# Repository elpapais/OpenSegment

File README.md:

OpenSegment Serial Display
==========================

[  
*OpenSegment Serial Display (Yellow) (COM-11645)*](https://www.sparkfun.com/products/11645)

OpenSegment is a ATmega328 based backpack for larger 7-segment displays. The ATmega receives data over digital interfaces (such as TWI, UART, SPI and buttons) and does all the PWM and upkeep of the display. 

Larger 7-segment displays pull more power than a microcontroller is able to drive directly. OpenSegment has 8 PNP and 4 NPN transistors in order to drive the segments at their maximum brightness.

**Features:**
* Standard FTDI connection
* Arduino Pro Mini @ 8MHz bootloader
* 5V functionality

This part was created in Eagle 6.3

Repository Contents
-------------------
* **/Hardware** - All Eagle design files and 3D files(.brd, .sch,)
* **/Production** - Test bed files and production panel files
* **Note:** Firmware is not included in this repo. Please see the [Serial7SegmentDisplay repo](https://github.com/sparkfun/Serial7SegmentDisplay) for the firmware. 

Product Versions
----------------
* [COM-11644](https://www.sparkfun.com/products/11644)- Red display
* [COM-11645](https://www.sparkfun.com/products/11645) - Yellow display
* [COM-11646](https://www.sparkfun.com/products/11646) - Green display
* [COM-11647](https://www.sparkfun.com/products/11647) - Blue display
* [COM-11648](https://www.sparkfun.com/products/11648) - White display

License Information
-------------------
The hardware is released under [Creative Commons Share-alike 3.0](http://creativecommons.org/licenses/by-sa/3.0/).

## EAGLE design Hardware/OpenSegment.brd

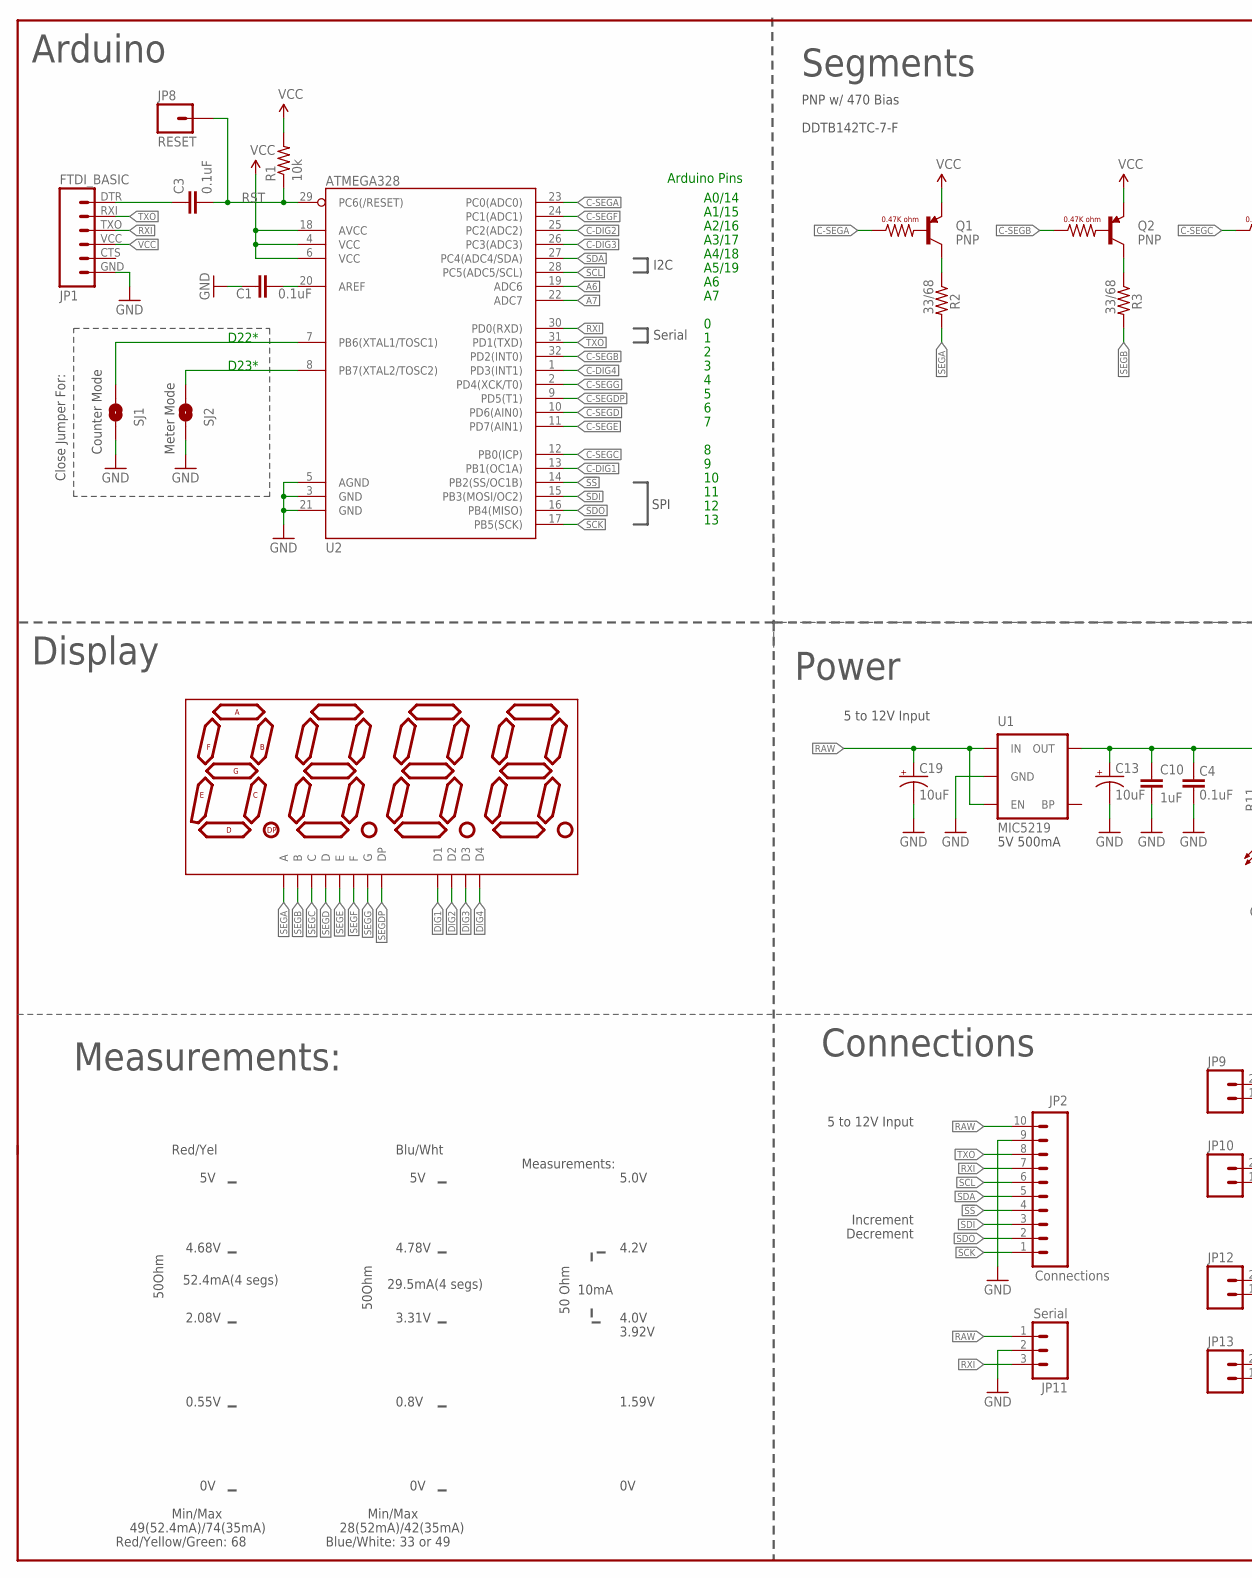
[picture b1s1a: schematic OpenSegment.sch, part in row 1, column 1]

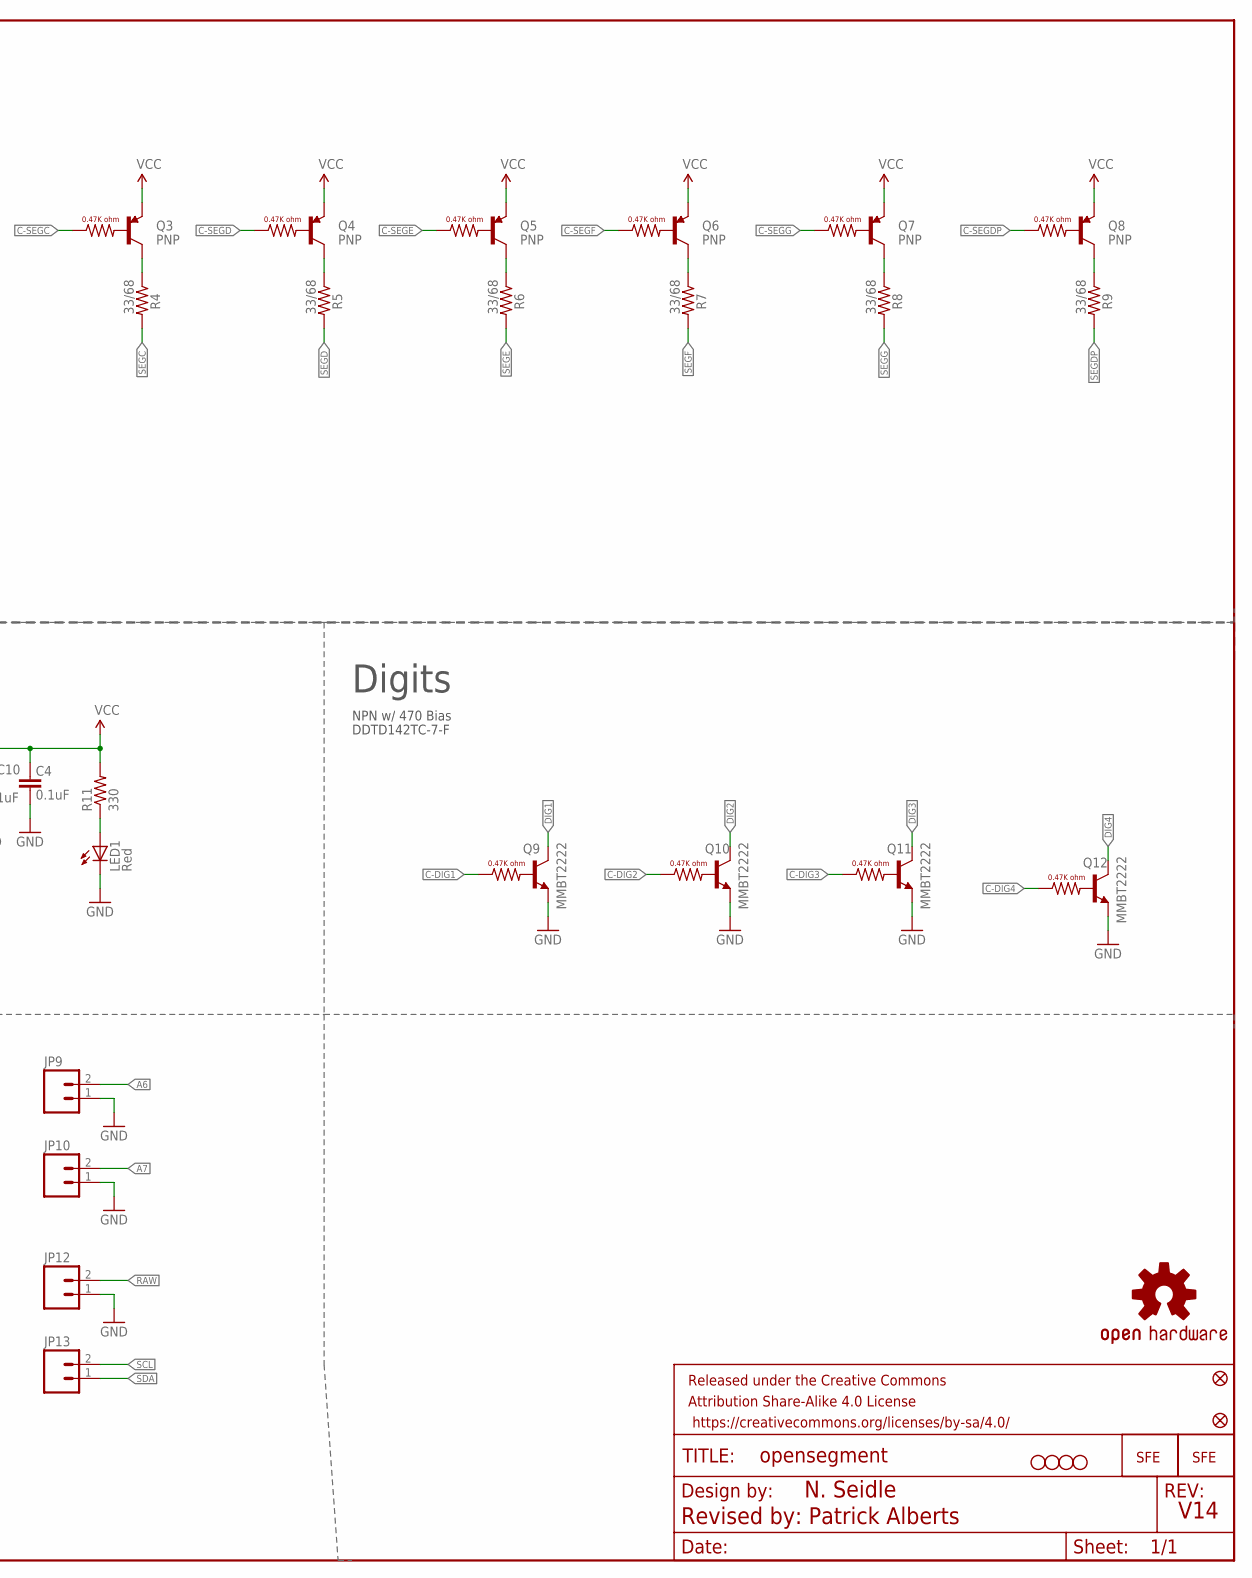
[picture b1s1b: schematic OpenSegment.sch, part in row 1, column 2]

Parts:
C1, C3, C4: 0.1uF; 0603-CAP
C10: 1uF; 0603-CAP
C13, C19: 10uF; EIA3216
FID1, FID2: FIDUCIAL1X2; FIDUCIAL-1X2
FRAME1: FRAME-LEDGER; CREATIVE_COMMONS
JP1: FTDI_BASIC
JP2: Connections; 1X10
JP3, JP4, JP5, JP6: STAND-OFF
JP8: RESET; 1X01
JP9, JP10, JP12, JP13: M02PTH; 1X02
JP11: Serial; JST-3-PTH
LED1: Red; LED-0603
Q1, Q2, Q3, Q4, Q5, Q6, Q7, Q8: PNP; SOT23-3
Q9, Q10, Q11, Q12: MMBT2222; SOT23-3
R1: 10k; 0603-RES
R2, R3, R4, R5, R6, R7, R8, R9: 33/68; 0603
R11: 330; 0603-RES
SJ1, SJ2: Counter Ctl; SJ_2S-NO
U1: MIC5219; SOT23-5
U2: ATMEGA328; TQFP32-08
U3: 7-SEGMENT-4DIGIT-COUNTERPTH; 7-SEGMENT-4DIGIT-COUNTER
U$2: LOGO-SFESK; SFE-LOGO-FLAME
U$4: OSHW-LOGOS; OSHW-LOGO-S
U$7: LOGO-SFENW2; SFE-NEW-WEB

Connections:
!SS: JP2.4, U2.14 (PB2(SS/OC1B))
A6: JP9.2, U2.19 (ADC6)
A7: JP10.2, U2.22 (ADC7)
ANALOG: SJ2.1, U2.8 (PB7(XTAL2/TOSC2))
C-DIG1: Q9.1 (B), U2.13 (PB1(OC1A))
C-DIG2: Q10.1 (B), U2.25 (PC2(ADC2))
C-DIG3: Q11.1 (B), U2.26 (PC3(ADC3))
C-DIG4: Q12.1 (B), U2.1 (PD3(INT1))
C-SEGA: Q1.1 (B), U2.23 (PC0(ADC0))
C-SEGB: Q2.1 (B), U2.32 (PD2(INT0))
C-SEGC: Q3.1 (B), U2.12 (PB0(ICP))
C-SEGD: Q4.1 (B), U2.10 (PD6(AIN0))
C-SEGDP: Q8.1 (B), U2.9 (PD5(T1))
C-SEGE: Q5.1 (B), U2.11 (PD7(AIN1))
C-SEGF: Q6.1 (B), U2.24 (PC1(ADC1))
C-SEGG: Q7.1 (B), U2.2 (PD4(XCK/T0))
COUNTER: SJ1.1, U2.7 (PB6(XTAL1/TOSC1))
DIG1: Q9.3 (C), U3.12 (D1)
DIG2: Q10.3 (C), U3.9 (D2)
DIG3: Q11.3 (C), U3.8 (D3)
DIG4: Q12.3 (C), U3.6 (D4)
GND: C1.1, C4.1, C10.2, C13.C (-), C19.C (-), JP1.GND (6), JP2.9, JP9.1, JP10.1, JP11.2, JP12.1, LED1.C, Q9.2 (E), Q10.2 (E), Q11.2 (E), Q12.2 (E), SJ1.2, SJ2.2, U1.2 (GND), U2.3 (GND), U2.5 (AGND), U2.21 (GND)
unnamed: Q1.3 (C), R2.1
unnamed: C3.1, JP1.DTR (1)
unnamed: Q2.3 (C), R3.1
unnamed: Q3.3 (C), R4.1
unnamed: Q4.3 (C), R5.1
unnamed: Q5.3 (C), R6.1
unnamed: Q6.3 (C), R7.1
unnamed: Q7.3 (C), R8.1
unnamed: Q8.3 (C), R9.1
unnamed: C1.2, U2.20 (AREF)
unnamed: LED1.A, R11.1
RAW: C19.A (+), JP2.10, JP11.1, JP12.2, U1.1 (IN), U1.3 (EN)
RST: C3.2, JP8.1, R1.1, U2.29 (PC6(/RESET))
RXI: JP1.TXO (3), JP2.7, JP11.3, U2.30 (PD0(RXD))
SCK: JP2.1, U2.17 (PB5(SCK))
SCL: JP2.6, JP13.2, U2.28 (PC5(ADC5/SCL))
SDA: JP2.5, JP13.1, U2.27 (PC4(ADC4/SDA))
SDI: JP2.3, U2.15 (PB3(MOSI/OC2))
SDO: JP2.2, U2.16 (PB4(MISO))
SEGA: R2.2, U3.11 (A)
SEGB: R3.2, U3.7 (B)
SEGC: R4.2, U3.4 (C)
SEGD: R5.2, U3.2 (D)
SEGDP: R9.2, U3.3 (DP)
SEGE: R6.2, U3.1 (E)
SEGF: R7.2, U3.10 (F)
SEGG: R8.2, U3.5 (G)
TXO: JP1.RXI (2), JP2.8, U2.31 (PD1(TXD))
VCC: C4.2, C10.1, C13.A (+), JP1.VCC (4), Q1.2 (E), Q2.2 (E), Q3.2 (E), Q4.2 (E), Q5.2 (E), Q6.2 (E), Q7.2 (E), Q8.2 (E), R1.2, R11.2, U1.5 (OUT), U2.4 (VCC), U2.6 (VCC), U2.18 (AVCC)

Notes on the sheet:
A0/14
A1/15
A2/16
A3/17
A4/18
A5/19
Arduino Pins
5V 500mA
SPI
Serial
I2C
Counter Mode
Arduino
Display
Segments
Digits
Connections
Power
D22*
D23*
4.2V
5.0V
4.0V
1.59V
3.92V
Measurements:
10mA
5 to 12V Input
Close Jumper For:
Meter Mode
Increment
Decrement
50 Ohm
4.78V
3.31V
0.8V
Blu/Wht
Red/Yel
4.68V
2.08V

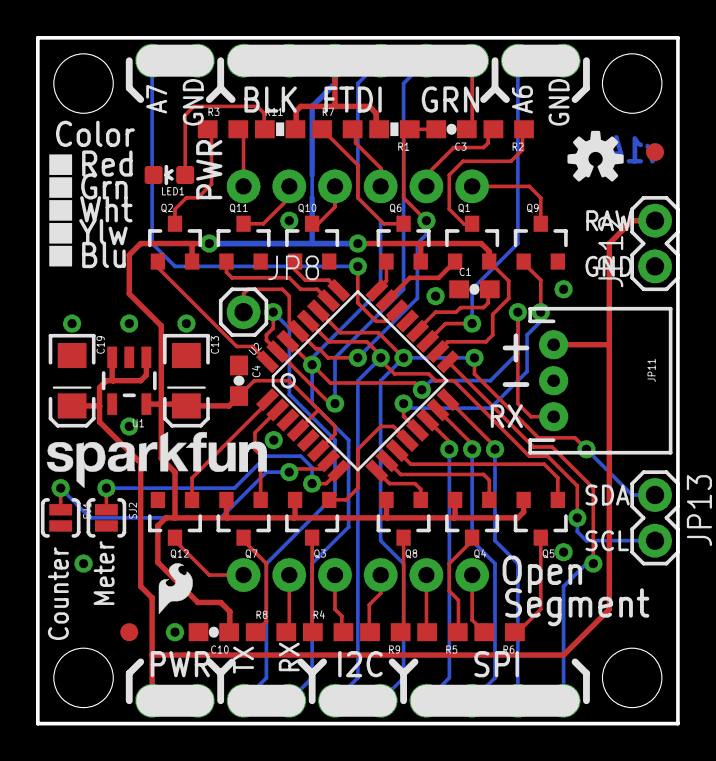
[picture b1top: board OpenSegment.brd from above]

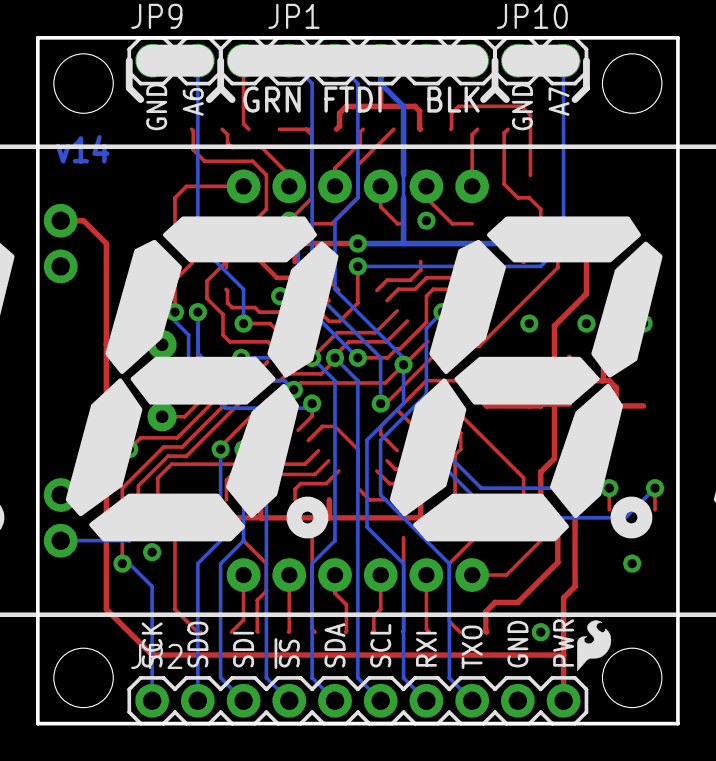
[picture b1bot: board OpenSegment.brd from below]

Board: 2 copper layers, 35.6 x 38.1 mm, 53 parts (6 on the bottom side), 51 nets.

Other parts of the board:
U$1: LOGO-SFESK; SFE-LOGO-FLAME

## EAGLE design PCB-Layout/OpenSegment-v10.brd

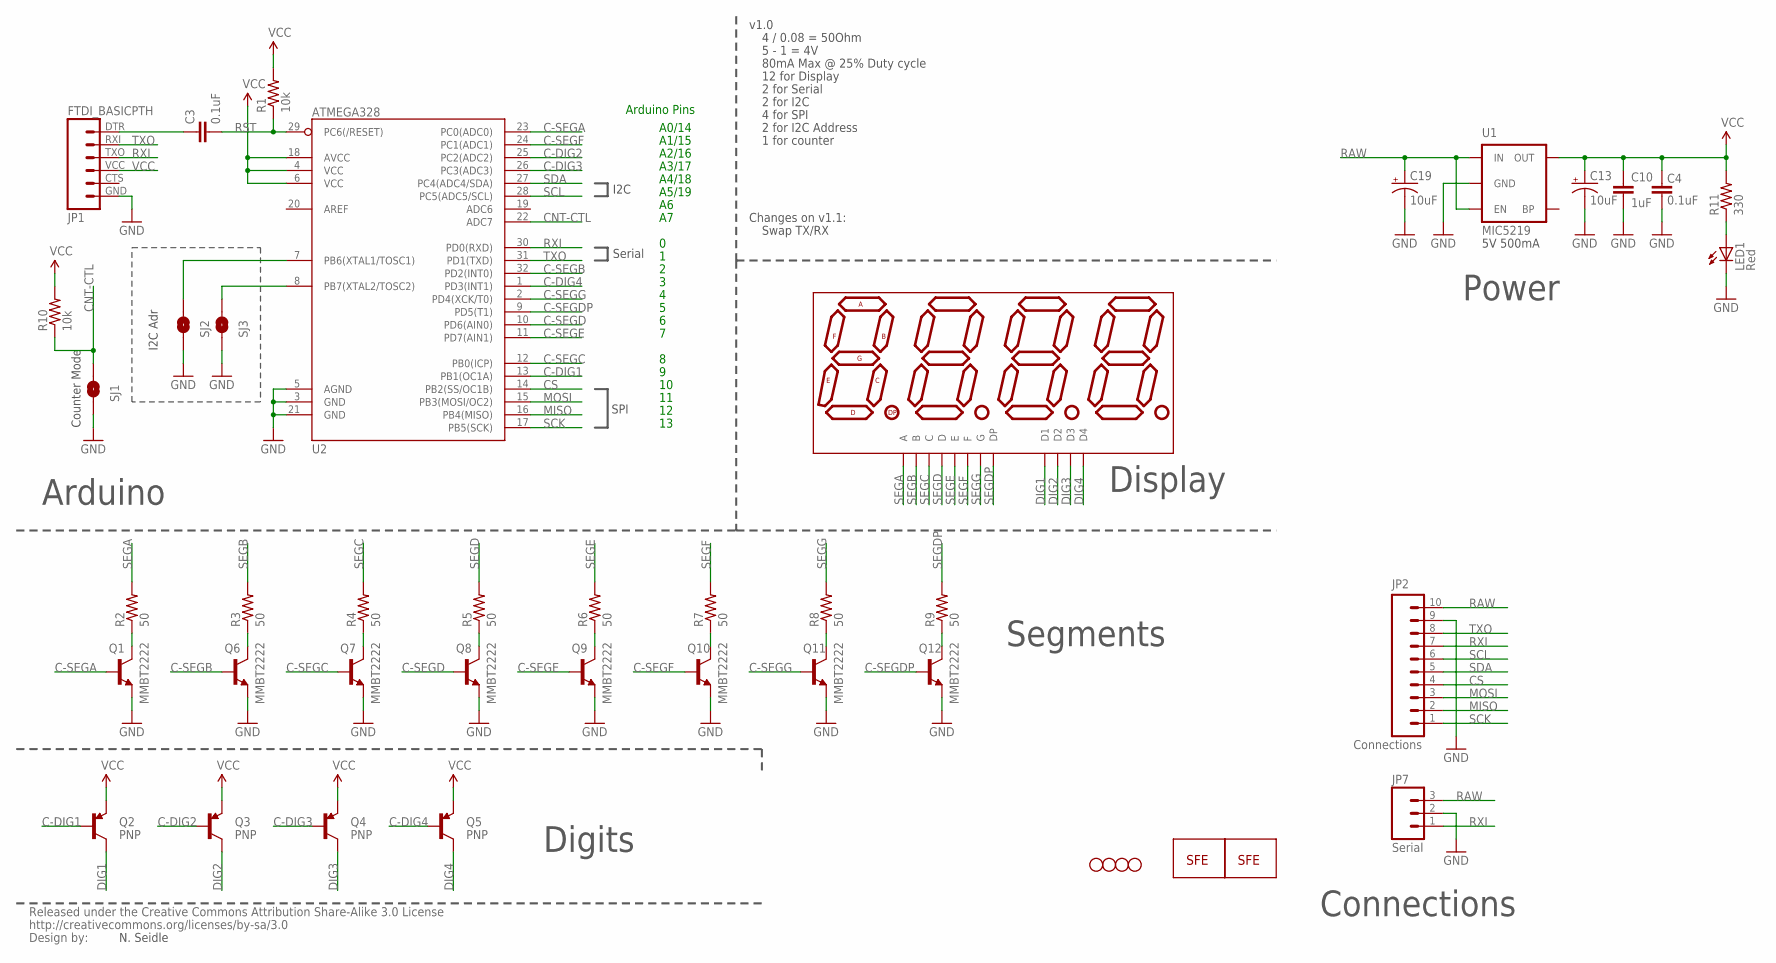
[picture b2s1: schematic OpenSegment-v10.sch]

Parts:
C3, C4: 0.1uF; 0402-CAP
C10: 1uF; 0402-CAP
C13, C19: 10uF; EIA3216
JP1: FTDI_BASICPTH; FTDI_BASIC
JP2: Connections; 1X10
JP3, JP4, JP5, JP6: STAND-OFF
JP7: Serial; JST-3-SMD
LED1: Red; LED-0603
Q1, Q6, Q7, Q8, Q9, Q10, Q11, Q12: MMBT2222; SOT23-3
Q2, Q3, Q4, Q5: PNP; SOT23-3
R1, R10: 10k; 0402-RES
R2, R3, R4, R5, R6, R7, R8, R9: 50; 0402-RES
R11: 330; 0402-RES
SJ1, SJ2, SJ3: Counter Ctl; SJ_2S-NO
U1: MIC5219; SOT23-5
U2: ATMEGA328; TQFP32-08
U3: 7-SEGMENT-4DIGIT-COUNTERPTH; 7-SEGMENT-4DIGIT-COUNTER
U$1: LOGO-SFESK; SFE-LOGO-FLAME
U$3: CREATIVE_COMMONS
U$7: LOGO-SFENW2; SFE-NEW-WEB

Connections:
C-DIG1: Q2.1 (B), U2.13 (PB1(OC1A))
C-DIG2: Q3.1 (B), U2.25 (PC2(ADC2))
C-DIG3: Q4.1 (B), U2.26 (PC3(ADC3))
C-DIG4: Q5.1 (B), U2.1 (PD3(INT1))
C-SEGA: Q1.1 (B), U2.23 (PC0(ADC0))
C-SEGB: Q6.1 (B), U2.32 (PD2(INT0))
C-SEGC: Q7.1 (B), U2.12 (PB0(ICP))
C-SEGD: Q8.1 (B), U2.10 (PD6(AIN0))
C-SEGDP: Q12.1 (B), U2.9 (PD5(T1))
C-SEGE: Q9.1 (B), U2.11 (PD7(AIN1))
C-SEGF: Q10.1 (B), U2.24 (PC1(ADC1))
C-SEGG: Q11.1 (B), U2.2 (PD4(XCK/T0))
CNT-CTL: R10.1, SJ1.1, U2.22 (ADC7)
CS: JP2.4, U2.14 (PB2(SS/OC1B))
DIG1: Q2.3 (C), U3.12 (D1)
DIG2: Q3.3 (C), U3.9 (D2)
DIG3: Q4.3 (C), U3.8 (D3)
DIG4: Q5.3 (C), U3.6 (D4)
GND: C4.1, C10.2, C13.C (-), C19.C (-), JP1.GND (6), JP2.9, JP7.2, LED1.C, Q1.2 (E), Q6.2 (E), Q7.2 (E), Q8.2 (E), Q9.2 (E), Q10.2 (E), Q11.2 (E), Q12.2 (E), SJ1.2, SJ2.2, SJ3.2, U1.2 (GND), U2.3 (GND), U2.5 (AGND), U2.21 (GND)
MISO: JP2.2, U2.16 (PB4(MISO))
MOSI: JP2.3, U2.15 (PB3(MOSI/OC2))
unnamed: Q1.3 (C), R2.1
unnamed: SJ3.1, U2.8 (PB7(XTAL2/TOSC2))
unnamed: C3.1, JP1.DTR (1)
unnamed: Q6.3 (C), R3.1
unnamed: Q7.3 (C), R4.1
unnamed: Q8.3 (C), R5.1
unnamed: Q9.3 (C), R6.1
unnamed: Q10.3 (C), R7.1
unnamed: Q11.3 (C), R8.1
unnamed: Q12.3 (C), R9.1
unnamed: SJ2.1, U2.7 (PB6(XTAL1/TOSC1))
unnamed: LED1.A, R11.1
RAW: C19.A (+), JP2.10, JP7.3, U1.1 (IN), U1.3 (EN)
RST: C3.2, R1.1, U2.29 (PC6(/RESET))
RXI: JP1.TXO (3), JP2.7, JP7.1, U2.30 (PD0(RXD))
SCK: JP2.1, U2.17 (PB5(SCK))
SCL: JP2.6, U2.28 (PC5(ADC5/SCL))
SDA: JP2.5, U2.27 (PC4(ADC4/SDA))
SEGA: R2.2, U3.11 (A)
SEGB: R3.2, U3.7 (B)
SEGC: R4.2, U3.4 (C)
SEGD: R5.2, U3.2 (D)
SEGDP: R9.2, U3.3 (DP)
SEGE: R6.2, U3.1 (E)
SEGF: R7.2, U3.10 (F)
SEGG: R8.2, U3.5 (G)
TXO: JP1.RXI (2), JP2.8, U2.31 (PD1(TXD))
VCC: C4.2, C10.1, C13.A (+), JP1.VCC (4), Q2.2 (E), Q3.2 (E), Q4.2 (E), Q5.2 (E), R1.2, R10.2, R11.2, U1.5 (OUT), U2.4 (VCC), U2.6 (VCC), U2.18 (AVCC)

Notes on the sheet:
N. Seidle
A0/14
A1/15
A2/16
A3/17
A4/18
A5/19
Arduino Pins
Changes on v1.1:
Swap TX/RX
5V 500mA
5 - 1 = 4V
80mA Max @ 25% Duty cycle
4 / 0.08 = 50Ohm
SPI
12 for Display
1 for counter
2 for I2C
4 for SPI
2 for Serial
v1.0
2 for I2C Address
Serial
I2C
I2C Adr
Counter Mode
Arduino
Display
Segments
Digits
Connections
Power

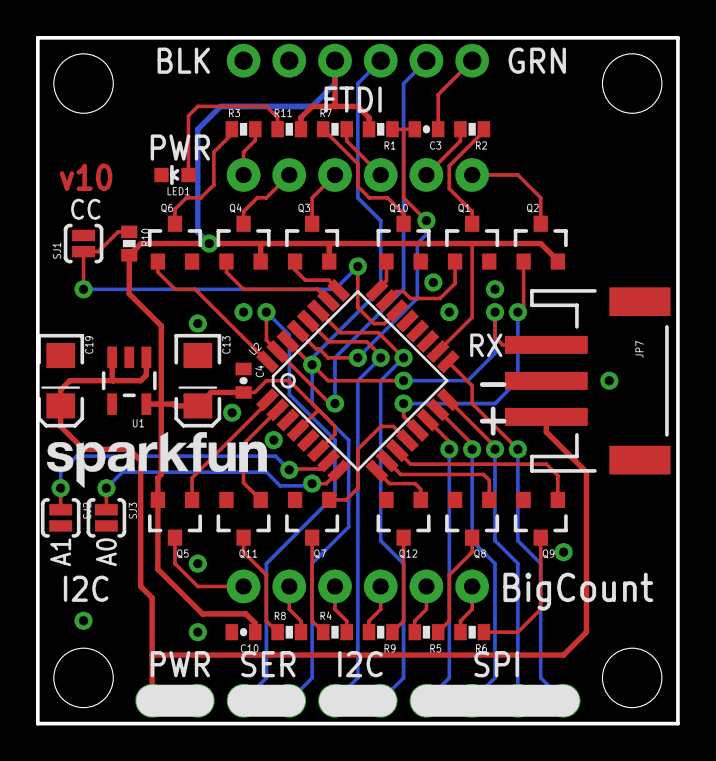
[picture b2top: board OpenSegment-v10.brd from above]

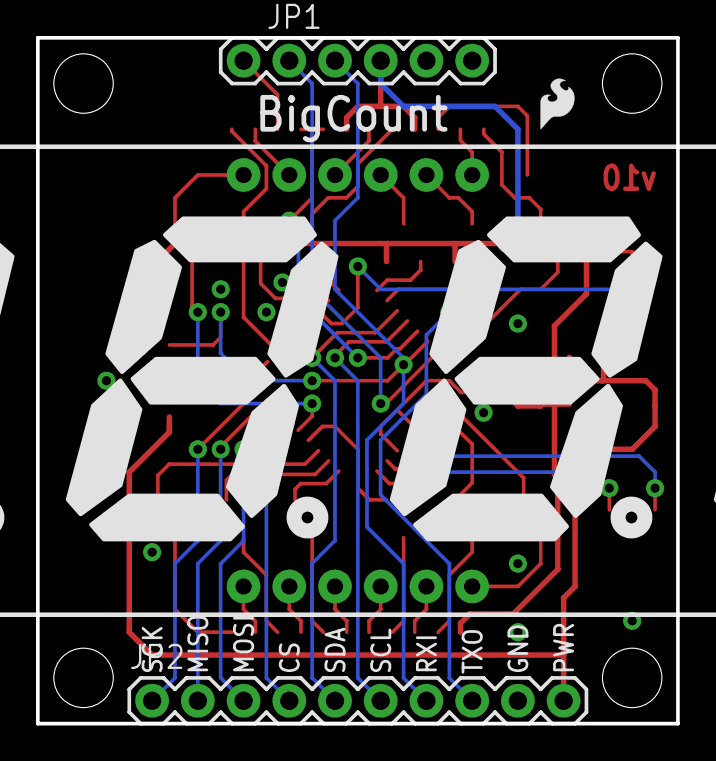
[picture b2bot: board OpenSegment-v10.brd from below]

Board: 2 copper layers, 35.6 x 38.1 mm, 45 parts (4 on the bottom side), 49 nets.

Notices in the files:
Firmware/OpenSegment/OpenSegment.ino:
This code is public domain but you buy me a beer if you use this and we meet someday (Beerware license).
parts and their libraries:
SparkFun-Displays: Licensing: CC v3.0 Share-Alike You are welcome to use this library for commercial purposes.
SparkFun-Aesthetics: Released under the Creative Commons Attribution Share-Alike 4.0 License
SparkFun-Aesthetics: https://creativecommons.org/licenses/by-sa/4.0
